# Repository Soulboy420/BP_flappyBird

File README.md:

# Flappy Bird auf ESP32-C3 — Bachelorprojekt HAW Hamburg

Hardware zum Projekt „Flappy Bird auf eigener ESP32-Baugruppe": zweilagige
Leiterplatte 72 × 51 mm, unbestückt zu beziehen und von Hand zu bestücken,
Display und Taster über JST-XH-Steckverbinder abgesetzt.

> **Vor der Bestellung:** Im Repository liegen nur die Quellen, keine
> Fertigungsunterlagen. Einmal `cd hardware && ./erzeugen.sh` auf einem
> Rechner mit KiCad 10 laufen lassen — das legt `ausgabe/` und `fertigung/`
> an und prüft dabei ERC, DRC und den Netzlistenabgleich mit.

## Alles erzeugen und prüfen

```bash
cd hardware && ./erzeugen.sh
```

Acht Schritte: Bibliotheken, Schaltplan, Platzierungsprüfung, Verdrahtung,
ERC und Netzlistenabgleich, Masseflächen füllen und DRC, Fertigungsunterlagen,
Prüfstand.

| Prüfung | Ergebnis |
|---|---|
| Prüfstand T1–T3, T5–T10, T12 (1618 Einzelprüfungen) | **0 Fehler** |
| Abstandsprüfung ohne KiCad (T6, 659 Kupferstücke paarweise) | **0 Unterschreitungen** |
| Durchgang ohne KiCad (T12, alle 36 Netze) | **0 offene Verbindungen** |
| Platzierung: Lötabstand, Rand, Sperrflächen, Kupferflächen | **0 Beanstandungen** |
| Abgleich Schaltplan ↔ Layout (unabhängig nachgerechnet) | **0 Abweichungen** |
| Reproduzierbarkeit | zweimal erzeugen ergibt bitgleiche Dateien |
| ERC, DRC, Gerber (T4, T11) | **noch offen** — braucht KiCad, siehe Kasten oben |

## Verzeichnisse

Im Repository liegen nur Quellen — alles Erzeugte entsteht aus ihnen neu.

```
hardware/
  flappy-esp32c3.kicad_pro / .kicad_sch / .kicad_pcb   Projektdateien
  erzeugen.sh                     erzeugt und prüft alles neu
  gen/                            Quellen des Entwurfs
  gen/tests.py, tests_stufe3.py   Prüfstand
  lib/                            projekteigene Symbole und Footprints
  fp-lib-table, sym-lib-table     damit KiCad lib/ findet
  doc/pruefbericht.md             Entwurfsprüfung: Befunde, Fläche, Gehäuse
  doc/pruefstand.md               was der Prüfstand prüft
  doc/pinbelegung.md              GPIO-Belegung, verbindlich für die Firmware
  doc/entscheidungen.md           Entwurfsentscheidungen und Abweichungen
  doc/inbetriebnahme.md           gestuftes Protokoll nach Projektplan 4.5
```

`./erzeugen.sh` legt zusätzlich an — beides bleibt bewusst außerhalb der
Versionsverwaltung, damit nie eine veraltete Fassung zur Bestellung geht:

```
  ausgabe/     Schaltplan-PDF, Layout-PDFs, Bestückungsplan, Stückliste,
               3D-Bild, ERC- und DRC-Bericht, exportierte Netzliste
  fertigung/   Gerber, Bohrdaten, Bestückungsdatei
```

## Kennzahlen

| | Revision A | Revision B |
|---|---|---|
| Platine | 90 × 60 mm (5400 mm²) | **72 × 51 mm (3672 mm², −32 %)** |
| Bauteile | 55 | 57 (43 bestückt, 10 Prüfpunkte, 4 Bohrungen M2) |
| Leiterbahnen | 371 Segmente, 843 mm | 413 Segmente, 723 mm |
| davon auf der Rückseite | 8,4 %, längstes Stück 10,8 mm | 10,5 %, längstes Stück **5,4 mm** |
| Durchkontaktierungen | 113 (82 Masse) | 86 (54 Masse) |
| kleinster Umrissabstand zwischen zwei Bauteilen | 0,15 mm | **0,82 mm** |
| kleinste Bahn / kleinster Abstand / kleinste Bohrung | 0,25 / 0,20 / 0,30 mm | unverändert |
| Kühlfläche am Laderegler | 114 mm², über eine Bahn angebunden | **122 mm², direkt am VBAT-Pad von U2** |

Zwei Lagen, 1,6 mm, Bestückung einseitig oben.

## Wie der Entwurf entsteht

Schaltplan und Layout sind **erzeugt**, nicht von Hand gezeichnet. Einzige
Wahrheitsquelle ist `gen/design.py` mit Bauteilen und Netzliste. Wer eine
Schaltungsänderung braucht, ändert diese Datei und lässt `./erzeugen.sh`
laufen — Schaltplan, Layout, Prüfungen und Fertigungsdaten entstehen neu.

Wer lieber in KiCad weiterzeichnet, kann das jederzeit tun; dann sollte
`erzeugen.sh` nicht mehr aufgerufen werden, sonst werden die Handänderungen
überschrieben.

## Handbestückung

Die Platine wird mit einer kleinen Lötstation von Hand bestückt. Dafür gilt
im Layout eine feste Regel, die `gen/chk_place.py` bei jedem Durchgang prüft:

* **mindestens 0,8 mm freier Abstand zwischen zwei Bauteilumrissen**
  (`LOETABSTAND` in `gen/layout_pcb.py`). Der Umriss der Handlöt-Footprints
  liegt schon 0,25 mm außerhalb der Pads — es bleiben also rund 1,3 mm
  freies Kupfer zwischen zwei benachbarten Pads, genug für eine
  1,6-mm-Meißelspitze.
* **mindestens 0,5 mm zum Platinenrand** (`RANDABSTAND`).
* alle SMD-Bauteile auf der Oberseite, alle im Handlöt-Footprint (0805
  statt 0603, verlängerte Pads am Funkmodul).

Schlägt eine dieser Regeln an, bricht `erzeugen.sh` ab.

## Vor der Bestellung

Vier Punkte am **gekauften** Bauteil nachmessen, siehe
`hardware/doc/entscheidungen.md` Abschnitt 3:

1. Pinbelegung des USB-C-Breakouts (erwartet VBUS, GND, D−, D+, CC1, CC2)
2. **Ob das Breakout schon 5,1-kΩ-Widerstände an CC1/CC2 trägt** — wenn ja,
   R17 und R18 **nicht** bestücken
3. Aderfolge des OLED-Moduls
4. Bauform des Schiebeschalters

## Werkzeug

KiCad 10 und Python 3 mit NumPy (für den Verdrahter). Der Generator schreibt
das KiCad-9-Format; der Füllschritt lässt KiCad die Platine in seinem eigenen
Format zurückschreiben. Wer KiCad 9 benutzt, lässt `erzeugen.sh` einmal auf
seinem Rechner laufen.

`erzeugen.sh` und `gen/design.py` suchen KiCad selbst — erst in den unten
genannten Umgebungsvariablen, dann im `PATH` bzw. in KiCads eigenen
`KICAD*_SYMBOL_DIR`/`KICAD*_FOOTPRINT_DIR`, dann an den üblichen
Installationsorten von macOS, Linux und Windows. Nur wenn das fehlschlägt,
muss von Hand nachgeholfen werden:

| Variable | wofür |
|---|---|
| `FLAPPY_KICAD_CLI` | Pfad zum Programm `kicad-cli` |
| `FLAPPY_KICAD_SYMBOLS` | Verzeichnis mit den `*.kicad_sym` der Standardbibliothek |
| `FLAPPY_KICAD_FOOTPRINTS` | Verzeichnis mit den `*.pretty` der Standardbibliothek |

Findet `erzeugen.sh` kein `kicad-cli`, bricht es gleich am Anfang mit einer
Meldung ab, statt eine halb erzeugte Platine zu hinterlassen.

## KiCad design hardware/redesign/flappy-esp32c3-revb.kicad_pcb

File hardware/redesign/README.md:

# Flappy Bird – Elektronik Revision B

Eigenständiger KiCad-10-Entwurf für das HAW-Bachelorprojekt. Der ursprüngliche Entwurf unter `hardware/` und absichtliche Benutzerlöschungen wurden nicht überschrieben. Es wurde nichts bestellt, committed oder gepusht.

**Status: NO-GO für eine Bestellfreigabe als fertiges Akkugerät.** Die digitalen Prüfungen bestehen; OLED-/Akku-Schnittstellen, Temperaturfreigabe, Gehäuse und Fertigeraufbau sind noch offen. R39 ist DNP und sperrt das Laden in der Standardbestückung. Die vollständigen Freigabebedingungen stehen in [doc/freigabe-checkliste.md](doc/freigabe-checkliste.md).

## Projekt öffnen

`flappy-esp32c3-revb.kicad_pro` mit KiCad 10.0.5 oder neuer öffnen. Hauptschaltplan und sechs hierarchische Funktionsblätter liegen daneben. Symbole, Footprints und 3D-Modelle sind unter `lib/` lokal eingebunden. Maßgeblich sind die gespeicherten nativen CAD-Dateien, nicht ein Generatorlauf. Das bestehende Firmwareprojekt wurde nicht auf die neue Pinbelegung umgestellt.

Das Layout ist 90×60 mm, zweilagig und 1,6 mm dick. Die ESP-Antenne ragt über die Oberkante. Überwiegend 0805/1206 und THT, mit begründeter lokaler Reflow-Ausnahme für den BQ24074 und anspruchsvoller USB-Buchsenbestückung.

## Inhalt

| Datei/Ordner | Zweck |
|---|---|
| `doc/audit.md` | Nachvollziehbare Fehler und Widersprüche im Ausgangsentwurf |
| `doc/designentscheidungen.md` | Tatsächliche Schaltung, Berechnungen, GPIOs, Betriebssequenzen, Ruhestrom und Grenzen |
| `doc/quellen.md` | Originaldatenblätter, Revisionen und Symbol-/Footprint-Pinprüfung |
| `doc/offene-annahmen.md` | Unbekannte reale Teile und DNP-Varianten |
| `doc/freigabe-checkliste.md` | Messungen vor Bestellung und gestufte Inbetriebnahme |
| `output/schaltplan.pdf` | Aktueller siebenseitiger Schaltplan, A3 |
| `output/pcb-oberseite.pdf`, `pcb-unterseite.pdf` | Kupfer/Bestückungsdruck, Unterseite gespiegelt, Maßstab 2,5:1 |
| `output/bestueckungsplan.pdf` | Kontrastreicher Plan mit Padnummern und DNP-Kreuzen, 2,5:1 |
| `output/stueckliste.csv` | Vollständige BOM mit Hersteller/MPN/Gehäuse/DNP |
| `output/pinmapping.csv` | Jede tatsächliche Pad-Netz-Zuordnung |
| `output/bestueckungspositionen.csv` | 85 zu bestückende Teile, Millimeter; DNP ausgeschlossen |
| `output/fertigung/` | Gerber X2, getrennte PTH-/NPTH-Bohrdaten und Bohrübersichten; noch keine Bestellfreigabe |
| `output/platine-3d.png`, `platine.step` | Ansicht und CAD-Geometrie zur Prüfung; U2/U3 haben vereinfachte Modelle |
| `verification/final-erc.*`, `final-drc.*` | Echte KiCad-Endberichte |
| `verification/consistency.json`, `pruefbericht.md` | Unabhängiger Datenabgleich und Prüfgrenzen |
| `verification/SHA256SUMS` | Dateihashes des Abgabestands |

## Ergebnis der digitalen Prüfung

KiCad 10.0.5: **ERC 0 Fehler/0 Warnungen; DRC 0 Fehler/0 Warnungen, 0 offene Verbindungen, 0 Schaltplan-Abweichungen**. Keine individuellen DRC-Ausnahmen. Abgleich aller 111 Referenzen und 58 Funktionsnetze bestanden; 85 bestückt, 26 DNP (darunter physische Testpads/Bohrungen). Detaillierte aktivierte bzw. standardmäßig nicht ausgeführte Prüfarten sind im Prüfbericht offengelegt.

## Weiterbearbeitung

Die Routingskripte unter `tools/` dokumentieren die Entwicklung und sind **keine idempotente Ein-Kommando-Neuerzeugung des fertigen Boards**. `build.py --update-board` setzt u.a. Bibliotheken und Beschriftungspositionen zurück. Nicht auf dem geprüften Endstand ausführen. Direkte KiCad-Bearbeitung ist der bevorzugte Weg; danach native ERC/DRC mit Neufüllung, XML-Netzexport, `verify_consistency.py` und sämtliche Ausgaben/Hashes neu erzeugen. `export_release.py` erzeugt nur die Abgabedateien aus bereits geprüften CAD-Dateien und prüft, dass der PCB-Inhalt beim Export unverändert bleibt. Die Skripte enthalten die hier verwendeten lokalen KiCad-Pfade und müssen auf einem anderen Rechner angepasst werden.

Die Schaltplanblätter verwenden globale Netzlabels und sind nach Funktionen gegliedert. Gleichnamige Labels sind elektrisch verbunden. Eine drahtlose Darstellung im Plan bedeutet keine fehlende Leiterbahn; die tatsächlichen Verbindungen stehen in der nativen Netzliste und wurden gegen das PCB geprüft.

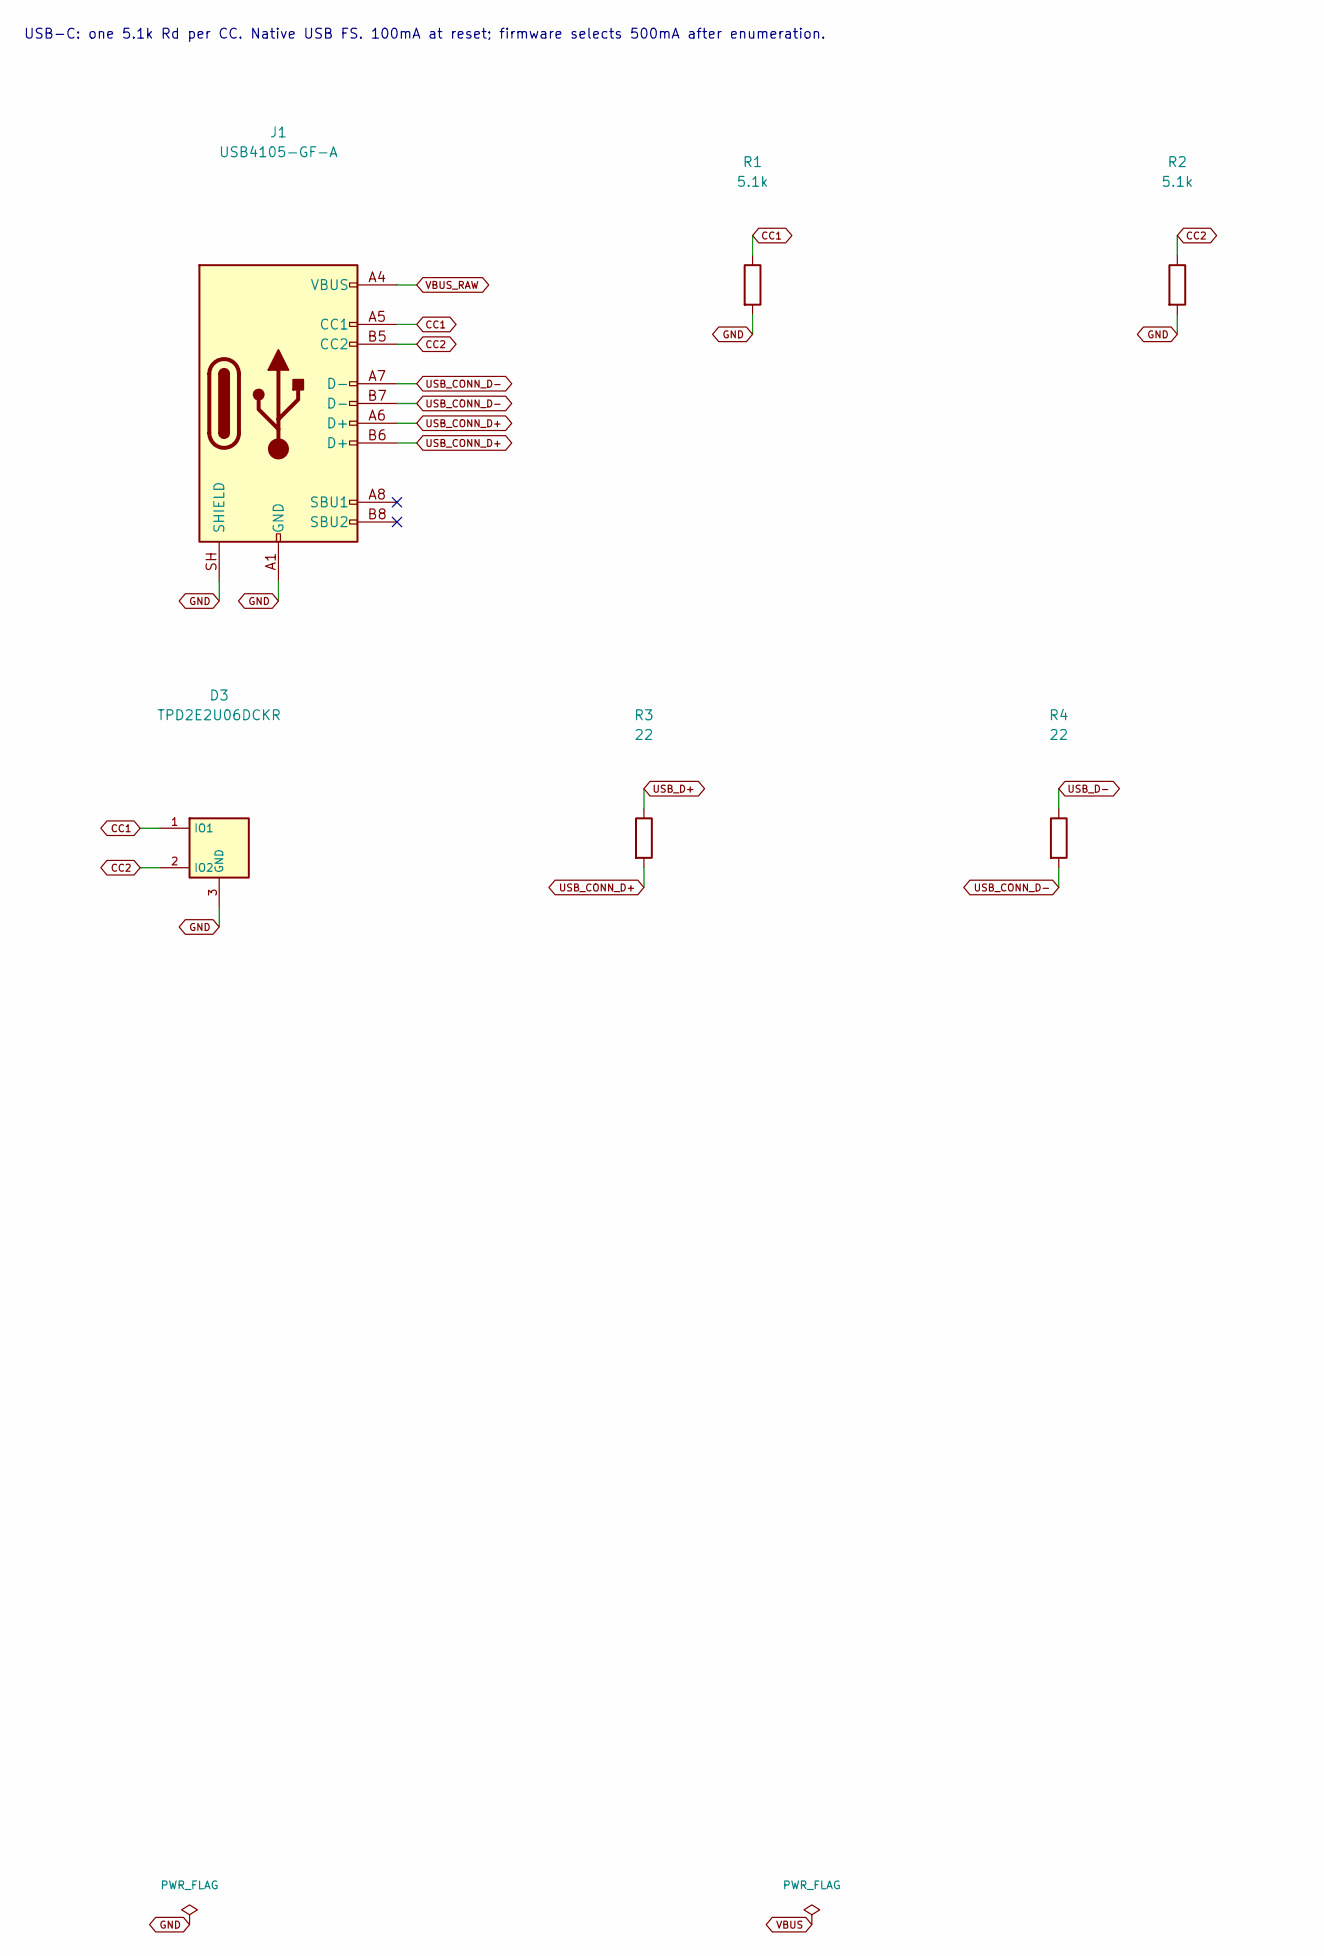
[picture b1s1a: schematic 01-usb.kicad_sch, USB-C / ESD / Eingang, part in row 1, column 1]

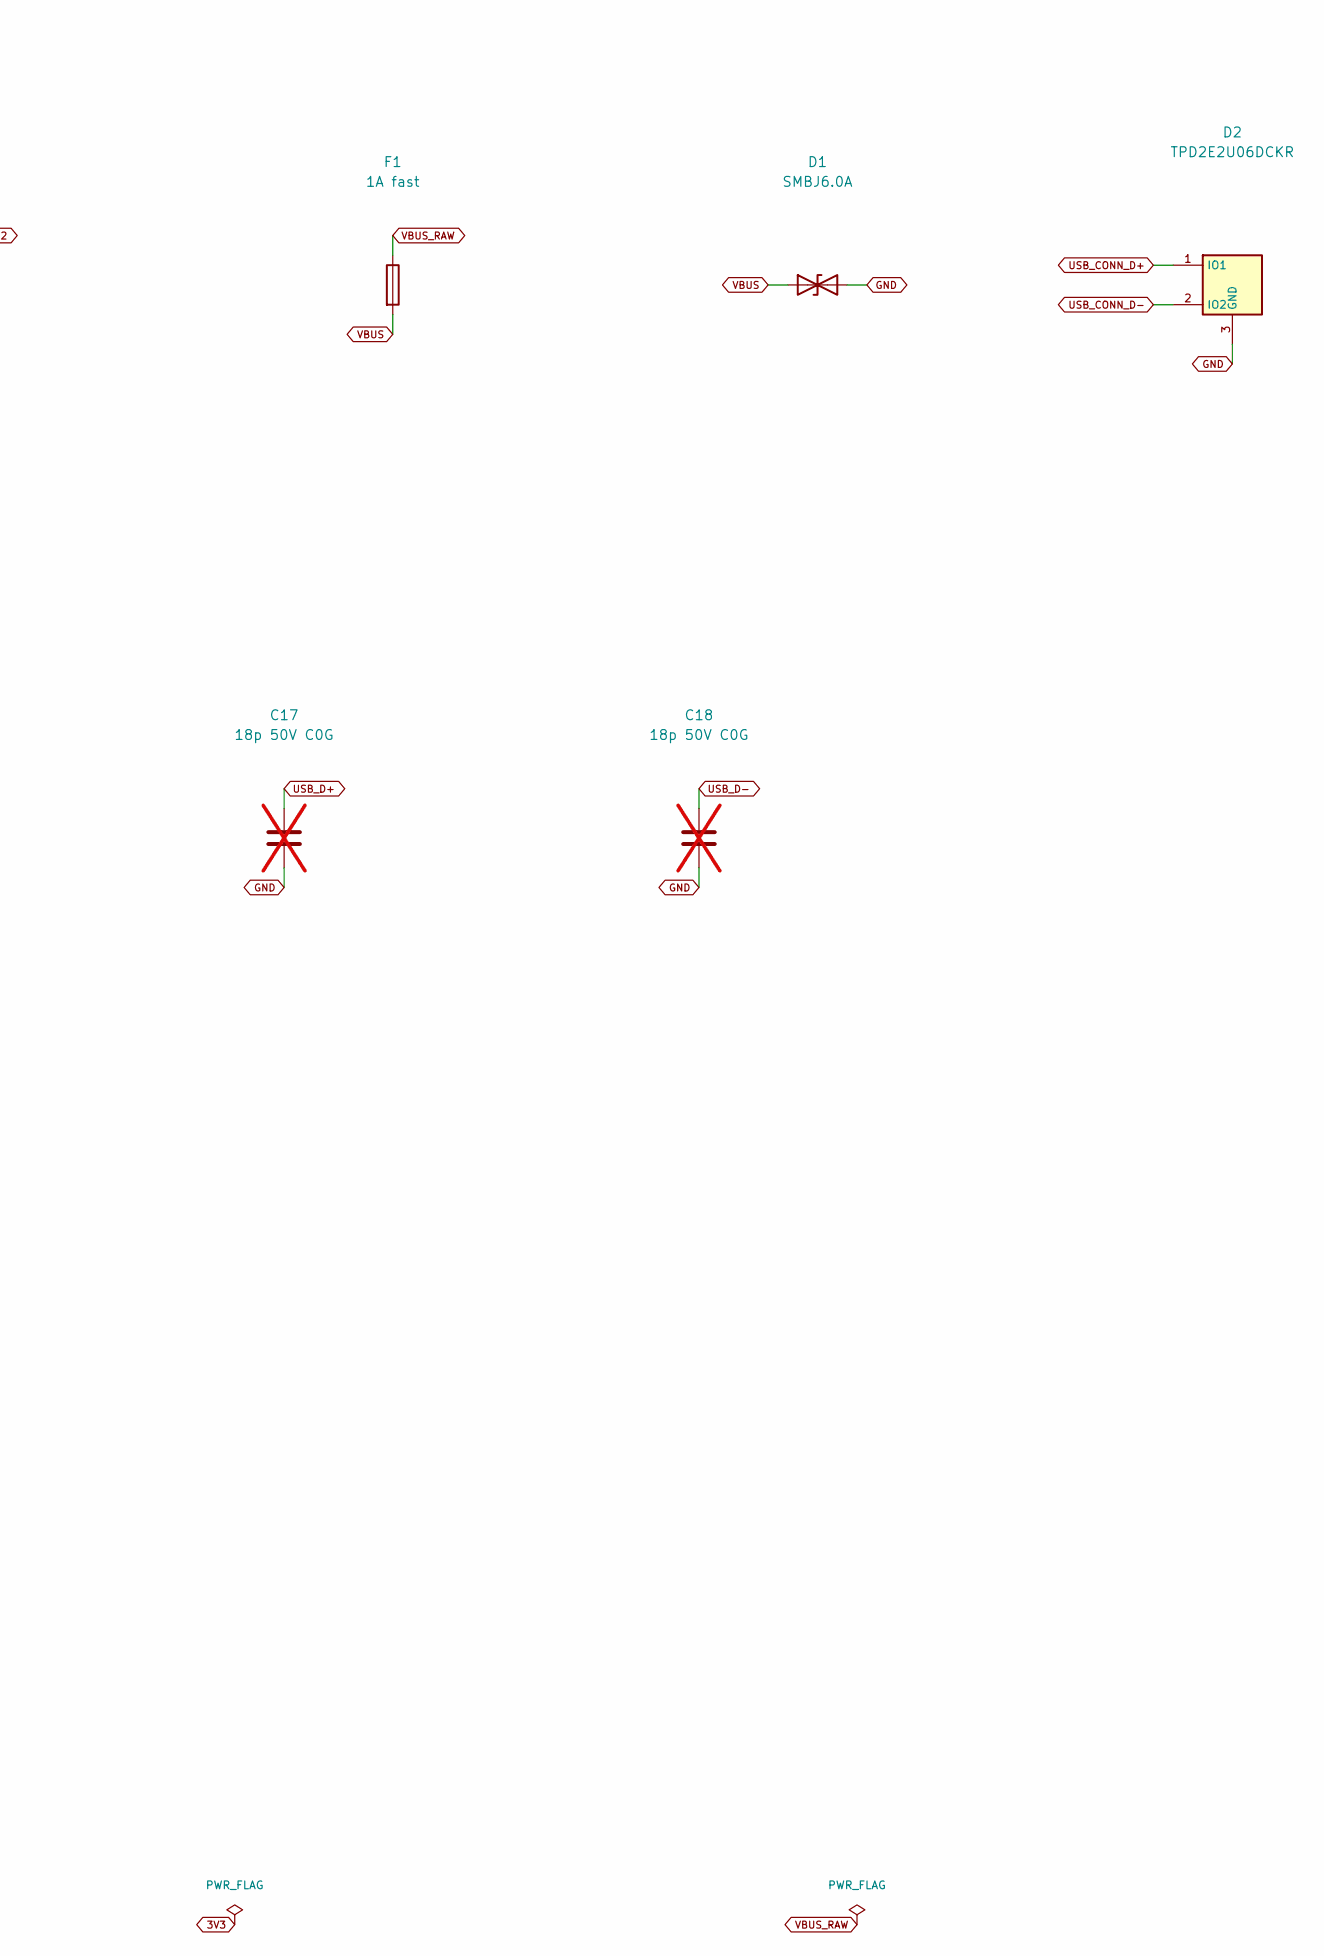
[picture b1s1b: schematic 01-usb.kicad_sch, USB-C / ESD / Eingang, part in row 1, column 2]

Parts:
C17, C18: 18p 50V C0G; Capacitor_SMD__C_0805_2012Metric_Pad1.18x1.45mm_HandSolder; MPN C0805C180J5GACTU; not fitted
D1: SMBJ6.0A; Diode_SMD__D_SMB; MPN SMBJ6.0A
D2, D3: TPD2E2U06DCKR; Package_TO_SOT_SMD__SOT-323_SC-70; MPN TPD2E2U06DCKR
F1: 1A fast; Fuse__Fuse_1206_3216Metric; MPN 0466001.NRHF
J1: USB4105-GF-A; Connector_USB__USB_C_Receptacle_GCT_USB4105-xx-A_16P_TopMnt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; MPN USB4105-GF-A
R1, R2: 5.1k; Resistor_SMD__R_0805_2012Metric_Pad1.20x1.40mm_HandSolder; MPN ERJ-6ENF5101V
R3, R4: 22; Resistor_SMD__R_0805_2012Metric_Pad1.20x1.40mm_HandSolder; MPN ERJ-6ENF22R0V

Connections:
CC1: D3.1 (IO1), J1.A5 (CC1), R1.1
CC2: D3.2 (IO2), J1.B5 (CC2), R2.1
GND: C17.2, C18.2, D1.2 (A2), D2.3 (GND), D3.3 (GND), J1.A1 (GND), J1.A12 (GND), J1.B1 (GND), J1.B12 (GND), J1.SH (SHIELD), R1.2, R2.2; also elsewhere on the board
USB_CONN_D+: D2.1 (IO1), J1.A6 (D+), J1.B6 (D+), R3.2
USB_CONN_D-: D2.2 (IO2), J1.A7 (D-), J1.B7 (D-), R4.2
USB_D+: C17.1, R3.1; also elsewhere on the board
USB_D-: C18.1, R4.1; also elsewhere on the board
VBUS: D1.1 (A1), F1.2; also elsewhere on the board
VBUS_RAW: F1.1, J1.A4 (VBUS), J1.A9 (VBUS), J1.B4 (VBUS), J1.B9 (VBUS)

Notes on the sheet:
USB-C: one 5.1k Rd per CC. Native USB FS. 100mA at reset; firmware selects 500mA after enumeration.

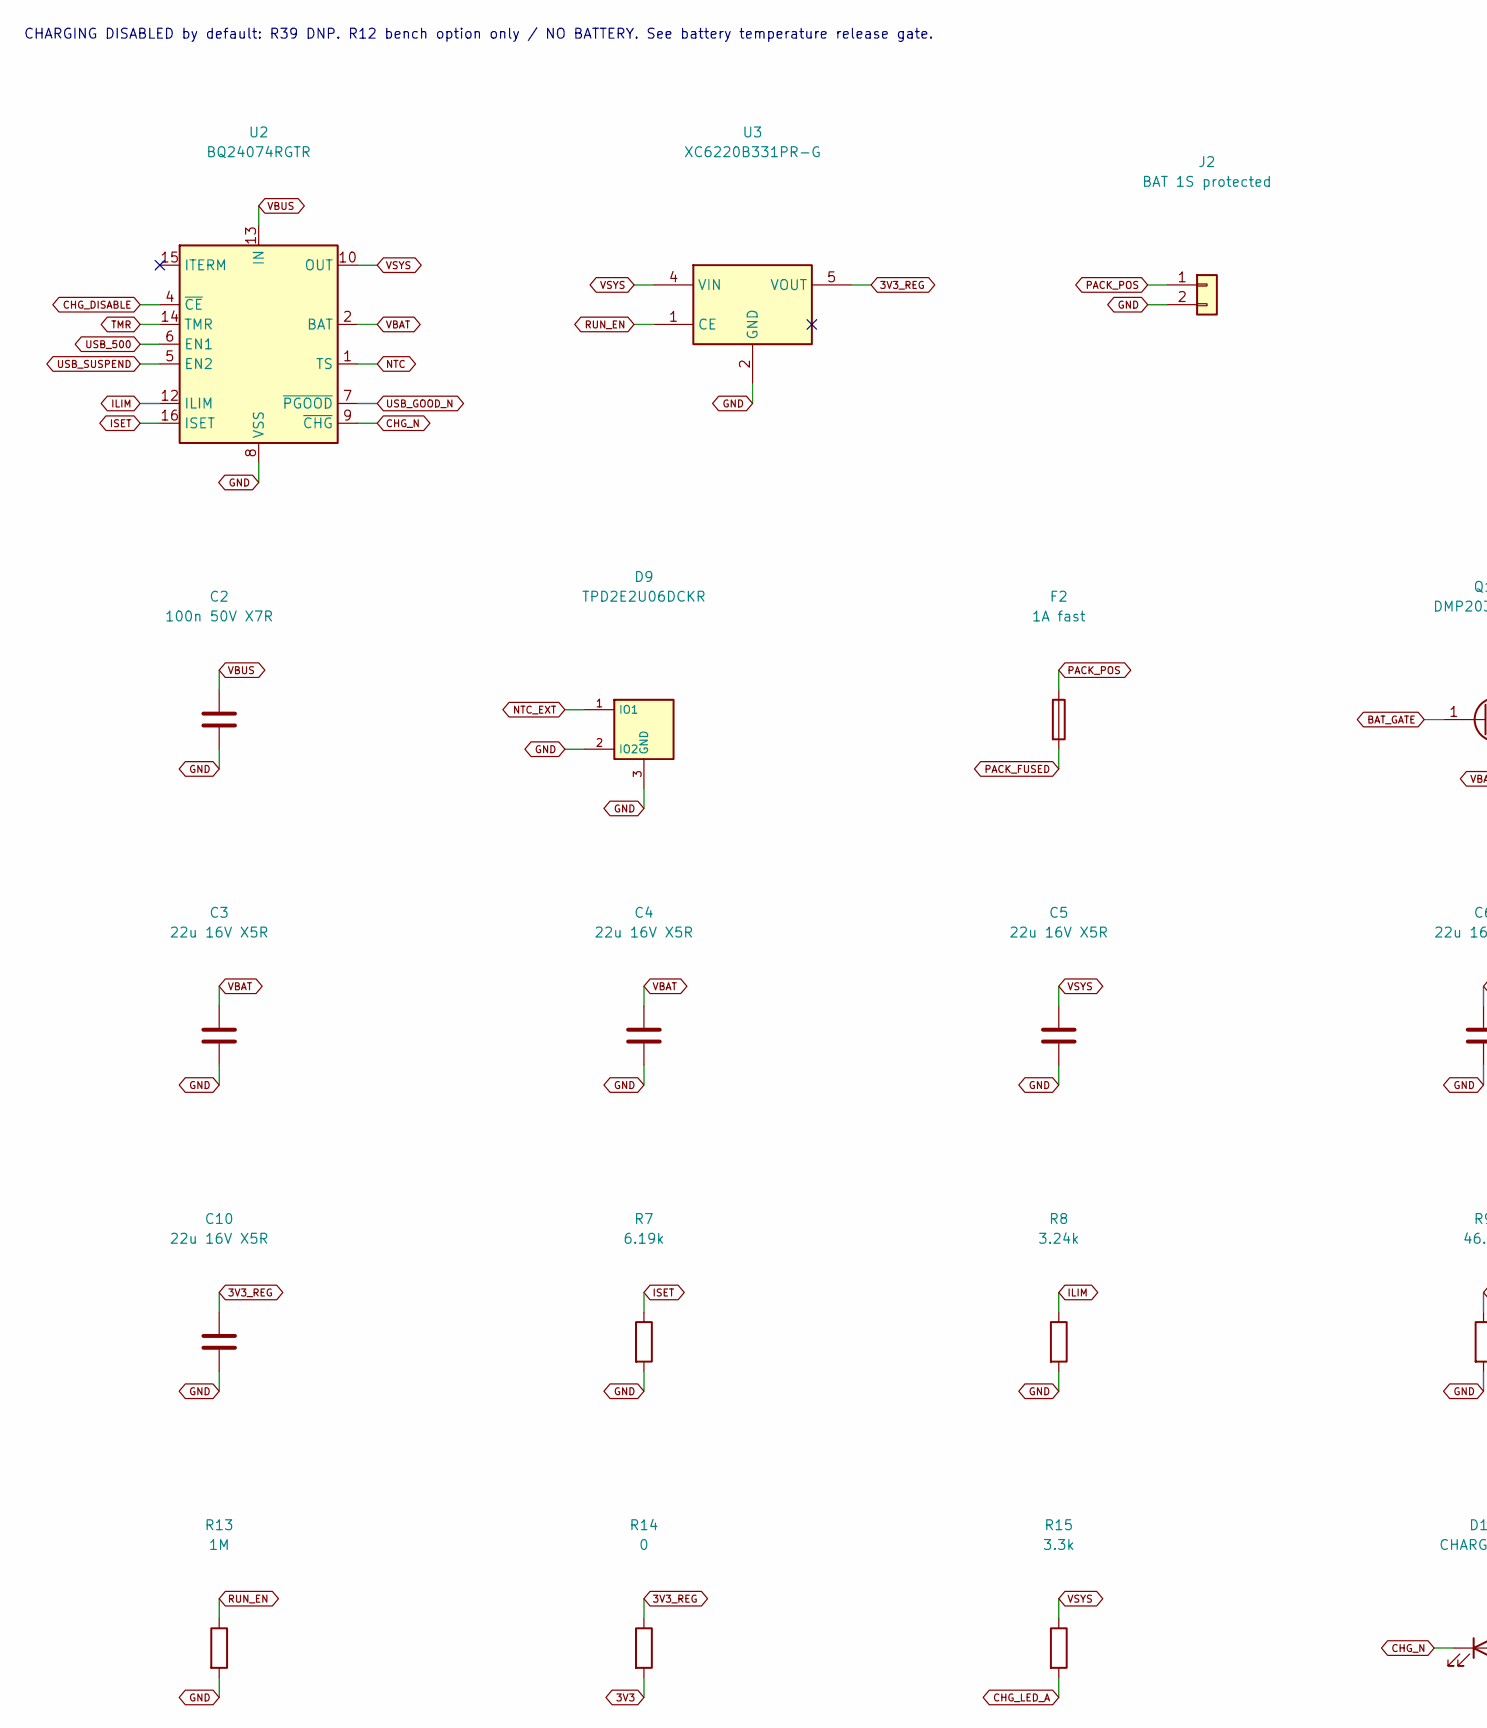
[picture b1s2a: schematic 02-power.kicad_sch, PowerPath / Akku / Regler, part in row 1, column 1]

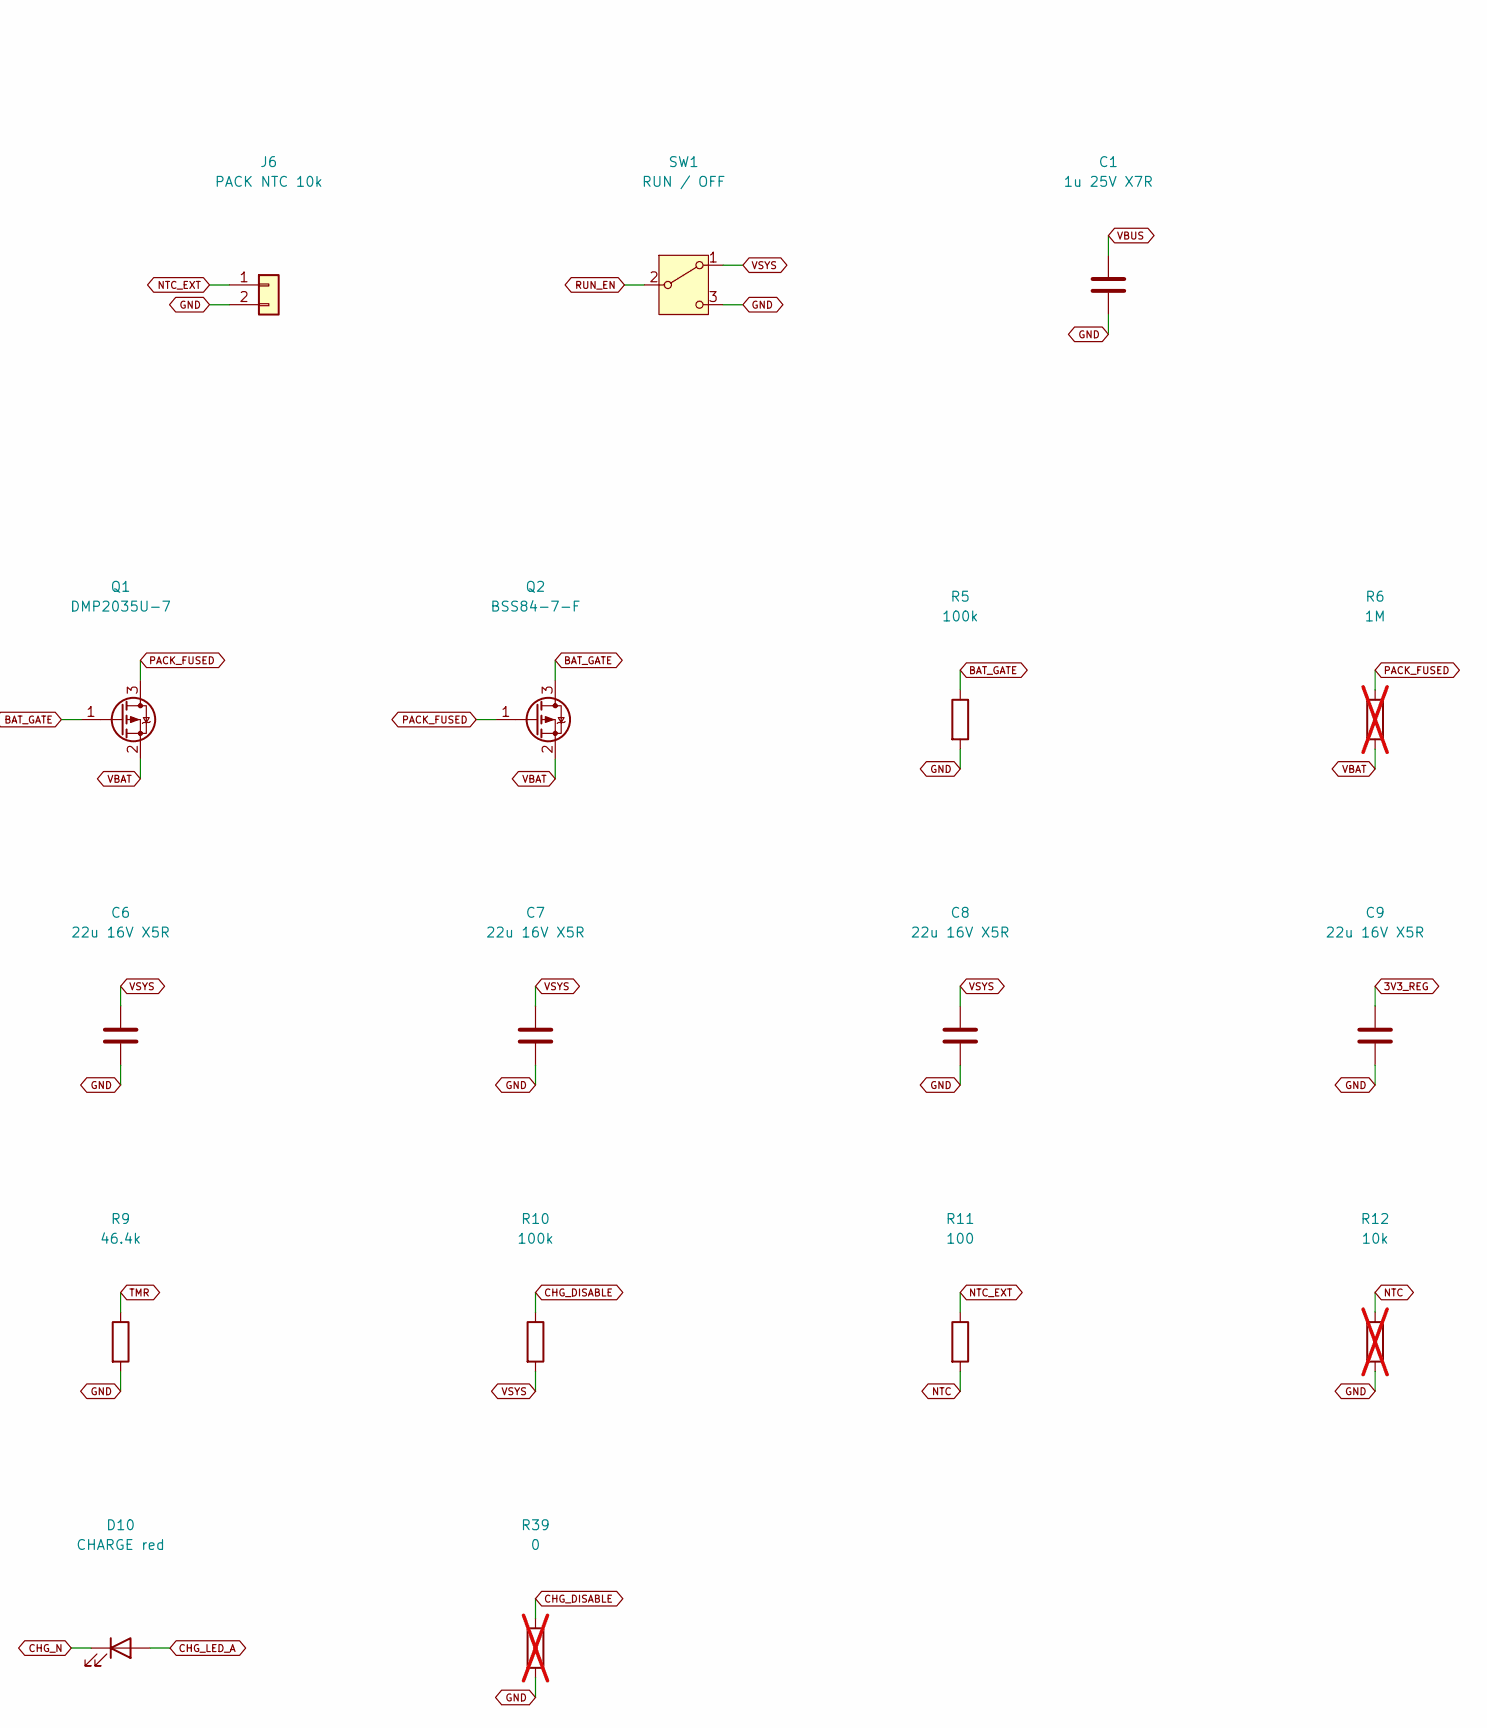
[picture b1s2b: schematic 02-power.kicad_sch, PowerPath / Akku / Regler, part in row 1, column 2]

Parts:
C1: 1u 25V X7R; Capacitor_SMD__C_0805_2012Metric_Pad1.18x1.45mm_HandSolder; MPN C2012X7R1E105K125AB
C2: 100n 50V X7R; Capacitor_SMD__C_0805_2012Metric_Pad1.18x1.45mm_HandSolder; MPN C2012X7R1H104K085AA
C3, C4, C5, C6, C7, C8, C9, C10: 22u 16V X5R; Capacitor_SMD__C_1206_3216Metric_Pad1.33x1.80mm_HandSolder; MPN C3216X5R1C226M160AB
D9: TPD2E2U06DCKR; Package_TO_SOT_SMD__SOT-323_SC-70; MPN TPD2E2U06DCKR
D10: CHARGE red; LED_SMD__LED_0805_2012Metric; MPN APT2012EC
F2: 1A fast; Fuse__Fuse_1206_3216Metric; MPN 0466001.NRHF
J2: BAT 1S protected; Connector_JST__JST_PH_B2B-PH-K_1x02_P2.00mm_Vertical; MPN B2B-PH-K-S(LF)(SN)
J6: PACK NTC 10k; Connector_JST__JST_PH_B2B-PH-K_1x02_P2.00mm_Vertical; MPN B2B-PH-K-S(LF)(SN)
Q1: DMP2035U-7; Package_TO_SOT_SMD__SOT-23; MPN DMP2035U-7
Q2: BSS84-7-F; Package_TO_SOT_SMD__SOT-23; MPN BSS84-7-F
R5, R10: 100k; Resistor_SMD__R_0805_2012Metric_Pad1.20x1.40mm_HandSolder; MPN ERJ-6ENF1003V
R6: 1M; Resistor_SMD__R_0805_2012Metric_Pad1.20x1.40mm_HandSolder; MPN ERJ-6ENF1004V; not fitted
R7: 6.19k; Resistor_SMD__R_0805_2012Metric_Pad1.20x1.40mm_HandSolder; MPN ERJ-6ENF6191V
R8: 3.24k; Resistor_SMD__R_0805_2012Metric_Pad1.20x1.40mm_HandSolder; MPN ERJ-6ENF3241V
R9: 46.4k; Resistor_SMD__R_0805_2012Metric_Pad1.20x1.40mm_HandSolder; MPN ERJ-6ENF4642V
R11: 100; Resistor_SMD__R_0805_2012Metric_Pad1.20x1.40mm_HandSolder; MPN ERJ-6ENF1000V
R12: 10k; Resistor_SMD__R_0805_2012Metric_Pad1.20x1.40mm_HandSolder; MPN ERJ-6ENF1002V; not fitted
R13: 1M; Resistor_SMD__R_0805_2012Metric_Pad1.20x1.40mm_HandSolder; MPN ERJ-6ENF1004V
R14: 0; Resistor_SMD__R_0805_2012Metric_Pad1.20x1.40mm_HandSolder; MPN ERJ-6GEY0R00V
R15: 3.3k; Resistor_SMD__R_0805_2012Metric_Pad1.20x1.40mm_HandSolder; MPN ERJ-6ENF3301V
R39: 0; Resistor_SMD__R_0805_2012Metric_Pad1.20x1.40mm_HandSolder; MPN ERJ-6GEY0R00V; not fitted
SW1: RUN / OFF; Button_Switch_THT__SW_Slide_SPDT_Straight_CK_OS102011MS2Q; MPN OS102011MS2QN1
U2: BQ24074RGTR; Package_DFN_QFN__VQFN-16-1EP_3x3mm_P0.5mm_EP1.6x1.6mm; MPN BQ24074RGTR
U3: XC6220B331PR-G; Package_TO_SOT_SMD__SOT-89-5; MPN XC6220B331PR-G

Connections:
3V3: R14.2; also elsewhere on the board
3V3_REG: C9.1, C10.1, R14.1, U3.5 (VOUT); also elsewhere on the board
BAT_GATE: Q1.1 (G), Q2.3 (D), R5.1
CHG_DISABLE: R10.1, R39.1, U2.4 (~CE); also elsewhere on the board
CHG_LED_A: D10.2 (A), R15.2
CHG_N: D10.1 (K), U2.9 (~CHG)
GND: C1.2, C2.2, C3.2, C4.2, C5.2, C6.2, C7.2, C8.2, C9.2, C10.2, D9.2 (IO2), D9.3 (GND), J2.2, J6.2, R5.2, R7.2, R8.2, R9.2, R12.2, R13.2, R39.2, SW1.3 (C), U2.8 (VSS), U2.17 (VSS), U3.2 (GND); also elsewhere on the board
ILIM: R8.1, U2.12 (ILIM)
ISET: R7.1, U2.16 (ISET); also elsewhere on the board
NTC: R11.2, R12.1, U2.1 (TS); also elsewhere on the board
NTC_EXT: D9.1 (IO1), J6.1, R11.1
PACK_FUSED: F2.2, Q1.3 (D), Q2.1 (G), R6.1
PACK_POS: F2.1, J2.1
RUN_EN: R13.1, SW1.2 (B), U3.1 (CE)
TMR: R9.1, U2.14 (TMR)
USB_500: U2.6 (EN1); also elsewhere on the board
USB_GOOD_N: U2.7 (~PGOOD); also elsewhere on the board
USB_SUSPEND: U2.5 (EN2); also elsewhere on the board
VBAT: C3.1, C4.1, Q1.2 (S), Q2.2 (S), R6.2, U2.2 (BAT), U2.3 (BAT); also elsewhere on the board
VBUS: C1.1, C2.1, U2.13 (IN); also elsewhere on the board
VSYS: C5.1, C6.1, C7.1, C8.1, R10.2, R15.1, SW1.1 (A), U2.10 (OUT), U2.11 (OUT), U3.4 (VIN); also elsewhere on the board

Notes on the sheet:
CHARGING DISABLED by default: R39 DNP. R12 bench option only / NO BATTERY. See battery temperature release gate.

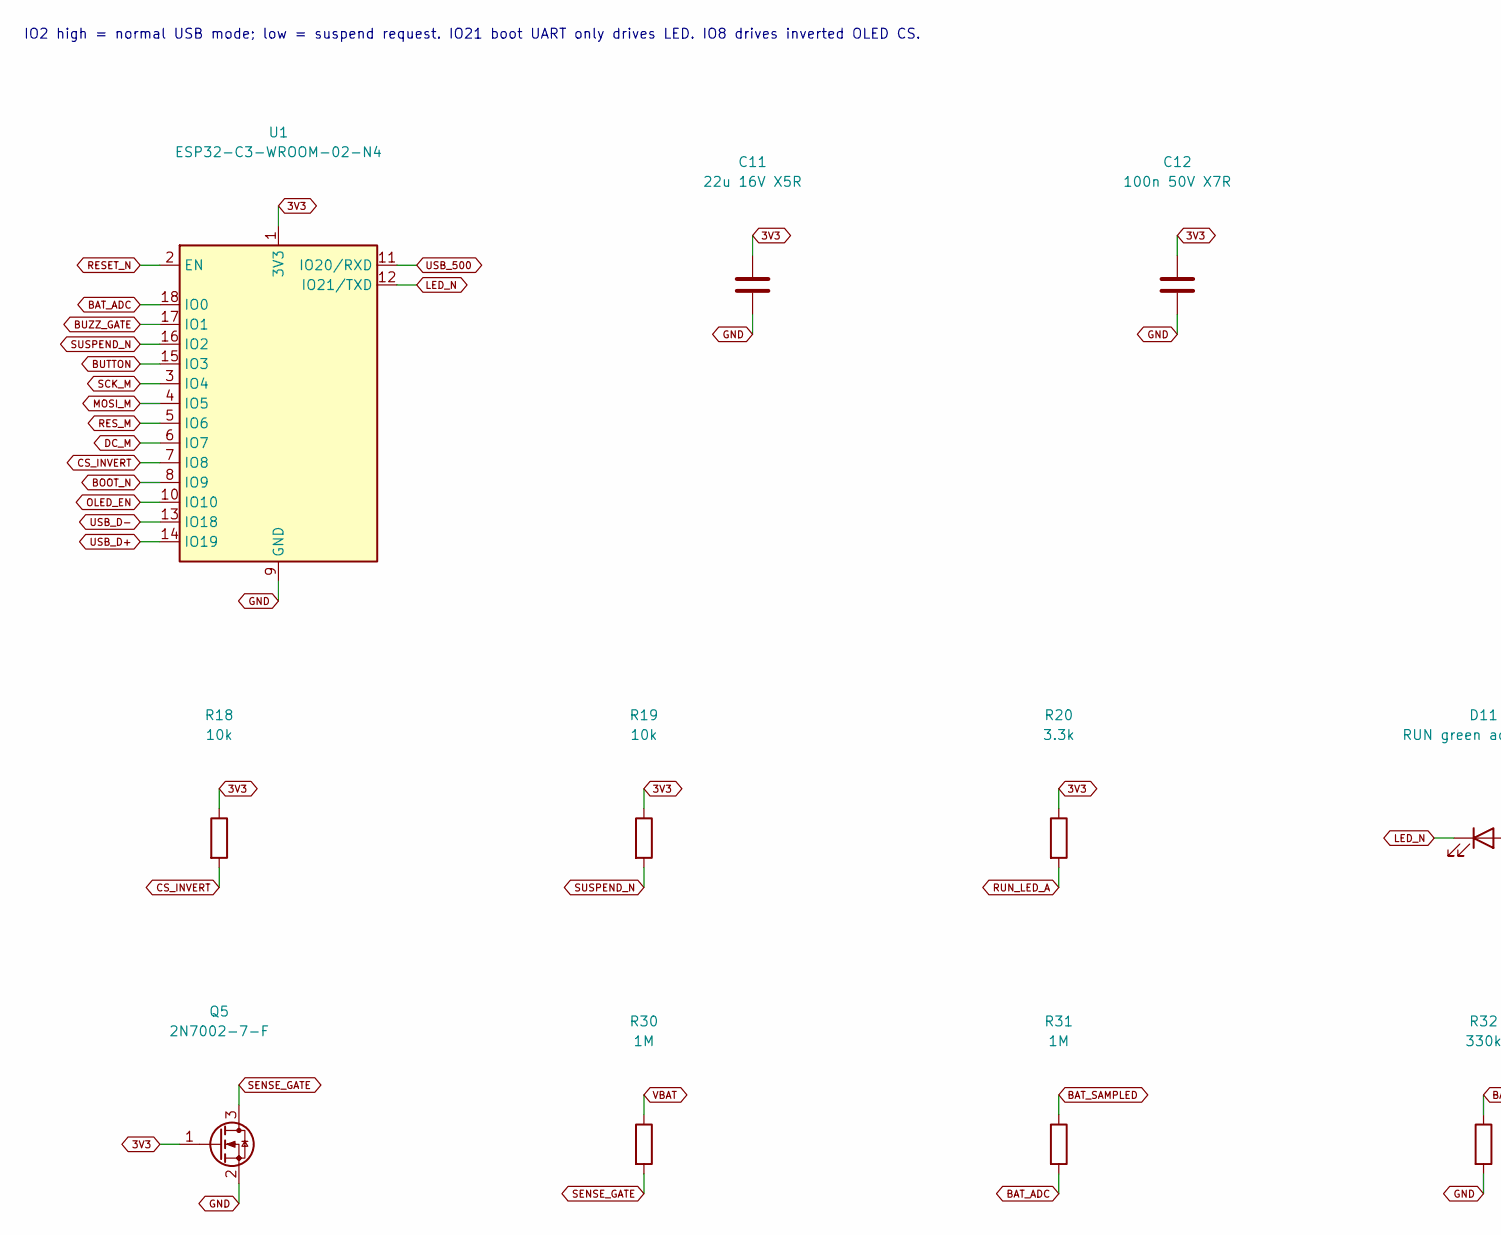
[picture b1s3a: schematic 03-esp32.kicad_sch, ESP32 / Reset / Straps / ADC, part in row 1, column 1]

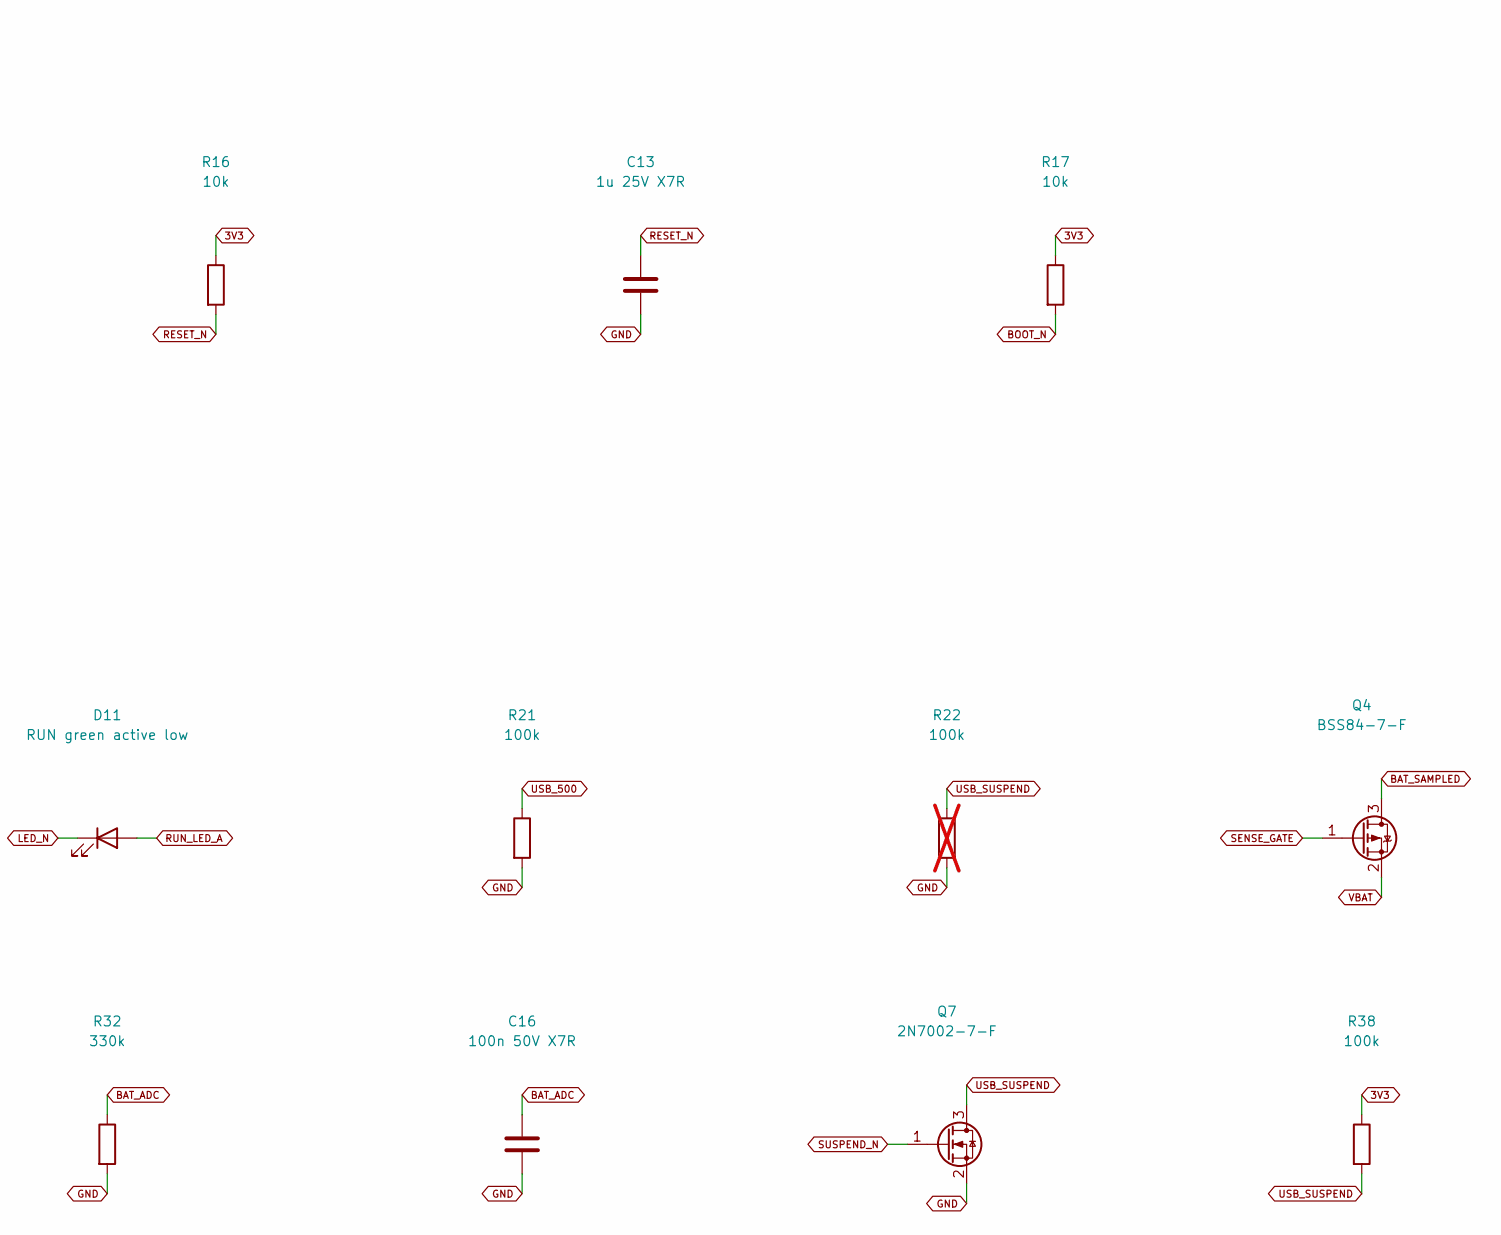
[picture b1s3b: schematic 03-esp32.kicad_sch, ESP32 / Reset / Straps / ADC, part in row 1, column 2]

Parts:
C11: 22u 16V X5R; Capacitor_SMD__C_1206_3216Metric_Pad1.33x1.80mm_HandSolder; MPN C3216X5R1C226M160AB
C12, C16: 100n 50V X7R; Capacitor_SMD__C_0805_2012Metric_Pad1.18x1.45mm_HandSolder; MPN C2012X7R1H104K085AA
C13: 1u 25V X7R; Capacitor_SMD__C_0805_2012Metric_Pad1.18x1.45mm_HandSolder; MPN C2012X7R1E105K125AB
D11: RUN green active low; LED_SMD__LED_0805_2012Metric; MPN APT2012SGC
Q4: BSS84-7-F; Package_TO_SOT_SMD__SOT-23; MPN BSS84-7-F
Q5, Q7: 2N7002-7-F; Package_TO_SOT_SMD__SOT-23; MPN 2N7002-7-F
R16, R17, R18, R19: 10k; Resistor_SMD__R_0805_2012Metric_Pad1.20x1.40mm_HandSolder; MPN ERJ-6ENF1002V
R20: 3.3k; Resistor_SMD__R_0805_2012Metric_Pad1.20x1.40mm_HandSolder; MPN ERJ-6ENF3301V
R21, R38: 100k; Resistor_SMD__R_0805_2012Metric_Pad1.20x1.40mm_HandSolder; MPN ERJ-6ENF1003V
R22: 100k; Resistor_SMD__R_0805_2012Metric_Pad1.20x1.40mm_HandSolder; MPN ERJ-6ENF1003V; not fitted
R30, R31: 1M; Resistor_SMD__R_0805_2012Metric_Pad1.20x1.40mm_HandSolder; MPN ERJ-6ENF1004V
R32: 330k; Resistor_SMD__R_0805_2012Metric_Pad1.20x1.40mm_HandSolder; MPN ERJ-6ENF3303V
U1: ESP32-C3-WROOM-02-N4; RF_Module__ESP32-C3-WROOM-02; MPN ESP32-C3-WROOM-02-N4

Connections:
3V3: C11.1, C12.1, Q5.1 (G), R16.1, R17.1, R18.1, R19.1, R20.1, R38.1, U1.1 (3V3); also elsewhere on the board
BAT_ADC: C16.1, R31.2, R32.1, U1.18 (IO0); also elsewhere on the board
BAT_SAMPLED: Q4.3 (D), R31.1
BOOT_N: R17.2, U1.8 (IO9); also elsewhere on the board
BUTTON: U1.15 (IO3); also elsewhere on the board
BUZZ_GATE: U1.17 (IO1); also elsewhere on the board
CS_INVERT: R18.2, U1.7 (IO8); also elsewhere on the board
DC_M: U1.6 (IO7); also elsewhere on the board
GND: C11.2, C12.2, C13.2, C16.2, Q5.2 (S), Q7.2 (S), R21.2, R22.2, R32.2, U1.9 (GND), U1.19 (GND); also elsewhere on the board
LED_N: D11.1 (K), U1.12 (IO21/TXD)
MOSI_M: U1.4 (IO5); also elsewhere on the board
OLED_EN: U1.10 (IO10); also elsewhere on the board
RESET_N: C13.1, R16.2, U1.2 (EN); also elsewhere on the board
RES_M: U1.5 (IO6); also elsewhere on the board
RUN_LED_A: D11.2 (A), R20.2
SCK_M: U1.3 (IO4); also elsewhere on the board
SENSE_GATE: Q4.1 (G), Q5.3 (D), R30.2
SUSPEND_N: Q7.1 (G), R19.2, U1.16 (IO2)
USB_500: R21.1, U1.11 (IO20/RXD); also elsewhere on the board
USB_D+: U1.14 (IO19); also elsewhere on the board
USB_D-: U1.13 (IO18); also elsewhere on the board
USB_SUSPEND: Q7.3 (D), R22.1, R38.2; also elsewhere on the board
VBAT: Q4.2 (S), R30.1; also elsewhere on the board

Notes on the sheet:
IO2 high = normal USB mode; low = suspend request. IO21 boot UART only drives LED. IO8 drives inverted OLED CS.
